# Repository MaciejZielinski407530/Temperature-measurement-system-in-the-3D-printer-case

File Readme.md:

Projekt: **System pomiaru temperatury w obudowie drukarki 3D**

W repozytorium znajduje się implementacja oraz projekt PCB stworzonego systemu. Udostępniona została również pełna doukemntacja projektu.
Do poprawnego działania wymagane są dodatkowe bilbioteki:
 -  SevenSeg: [Github](https://github.com/sigvaldm/SevenSeg)
 -  DS18B20: [Github](https://github.com/matmunk/DS18B20)
 -  OneWire: [Github](https://github.com/PaulStoffregen/OneWire)

Projekt oraz dokumentację projektową sporządził:

***Maciej Zieliński***

***Akademia Górniczo-Hutnicza Kraków***

-----------------------------------------------------------------------------------------------
Project: **Temperature measurement system in the 3D printer case**

The repository contains implementation and PCB project of the created system. Full documentation of the project was also made available.
Additional libraries are required for proper operation:
 -  SevenSeg: [Github](https://github.com/sigvaldm/SevenSeg)
 -  DS18B20: [Github](https://github.com/matmunk/DS18B20)
 -  OneWire: [Github](https://github.com/PaulStoffregen/OneWire)

The project and documentation prepared by:

***Maciej Zieliński***

***Akademia Górniczo-Hutnicza Kraków***

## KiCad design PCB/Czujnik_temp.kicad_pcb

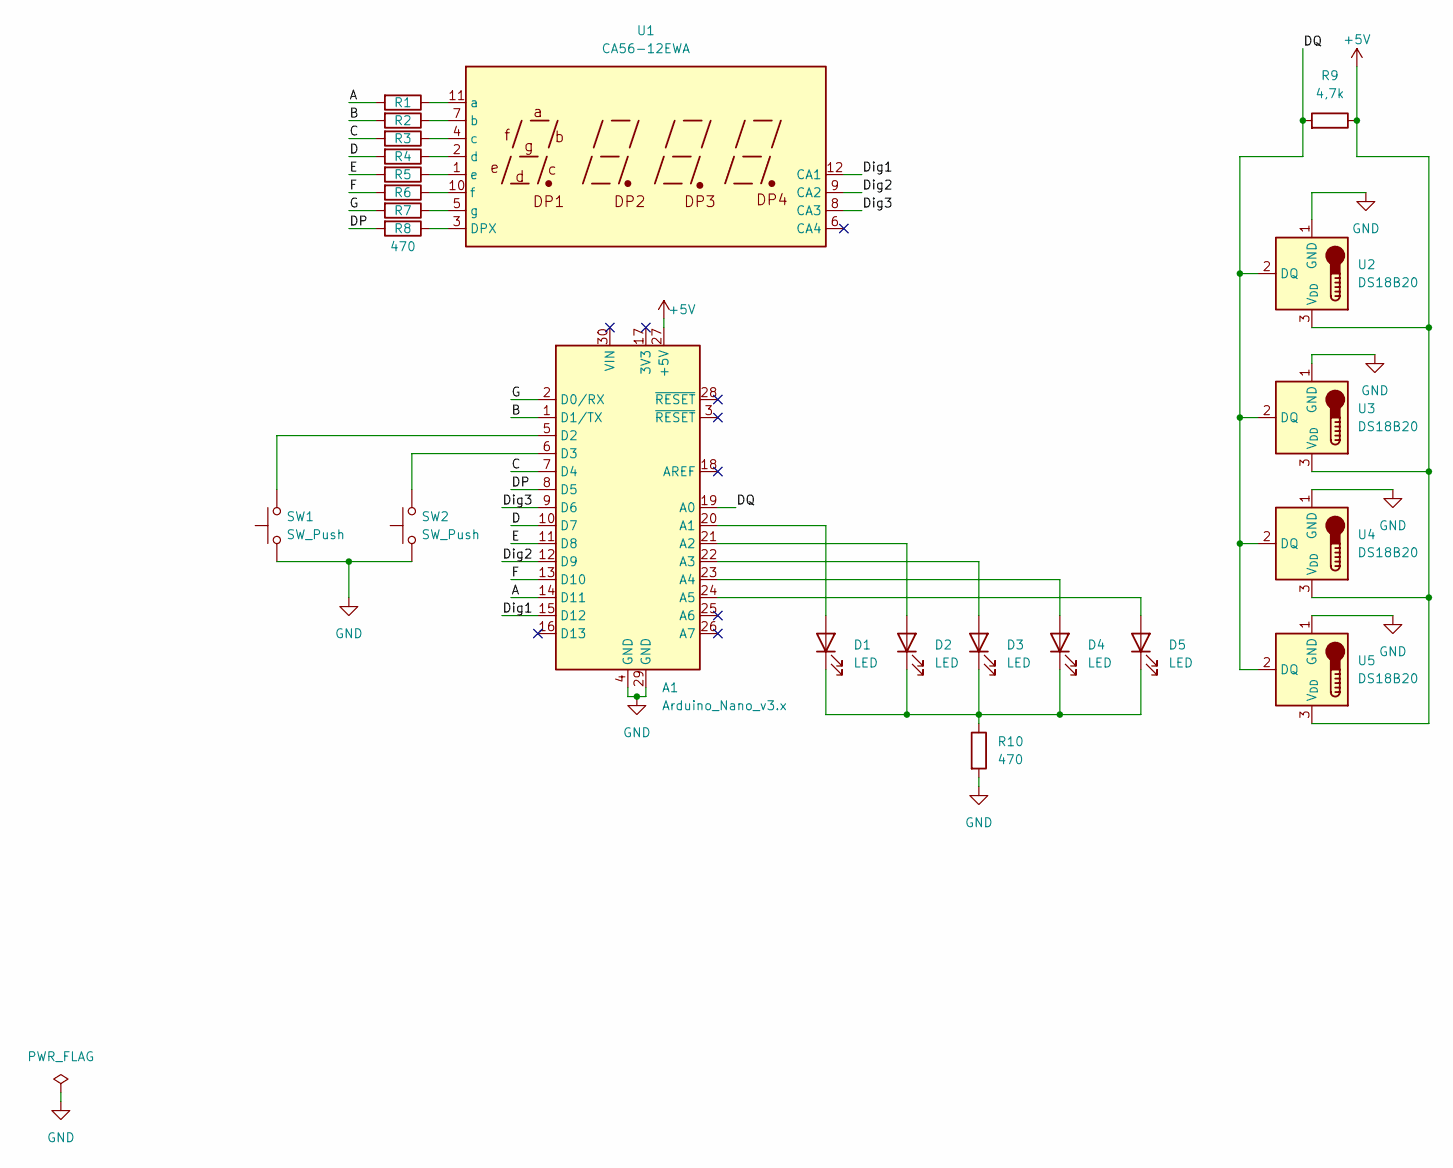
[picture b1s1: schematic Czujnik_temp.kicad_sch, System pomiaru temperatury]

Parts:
A1: Arduino_Nano_v3.x; Arduino_Nano
D1, D2, D3, D4, D5: LED; LED_D5.0mm
R1, R2, R3, R4, R5, R6, R8: R; R_Axial_DIN0207_L6.3mm_D2.5mm_P10.16mm_Horizontal
R7, R10: 470; R_Axial_DIN0207_L6.3mm_D2.5mm_P10.16mm_Horizontal
R9: 4,7k; R_Axial_DIN0207_L6.3mm_D2.5mm_P10.16mm_Horizontal
SW1, SW2: SW_Push; SW_PUSH_6mm_H9.5mm
U1: CA56-12EWA
U2, U3, U4, U5: DS18B20; TerminalBlock_bornier-3_P5.08mm

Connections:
+5V: A1.27 (+5V), R9.1, U2.3 (V_{DD}), U3.3 (V_{DD}), U4.3 (V_{DD}), U5.3 (V_{DD})
/A: A1.14 (D11), R1.2
/B: A1.1 (D1/TX), R2.2
/C: A1.7 (D4), R3.2
/D: A1.10 (D7), R4.2
/DP: A1.8 (D5), R8.2
/DQ: A1.19 (A0), R9.2, U2.2 (DQ), U3.2 (DQ), U4.2 (DQ), U5.2 (DQ)
/Dig1: A1.15 (D12), U1.12 (CA1)
/Dig2: A1.12 (D9), U1.9 (CA2)
/Dig3: A1.9 (D6), U1.8 (CA3)
/E: A1.11 (D8), R5.2
/F: A1.13 (D10), R6.2
/G: A1.2 (D0/RX), R7.2
GND: A1.4 (GND), A1.29 (GND), R10.2, SW1.1, SW2.1, U2.1 (GND), U3.1 (GND), U4.1 (GND), U5.1 (GND)
unnamed: A1.20 (A1), D1.2 (A)
unnamed: A1.21 (A2), D2.2 (A)
unnamed: A1.22 (A3), D3.2 (A)
unnamed: A1.23 (A4), D4.2 (A)
unnamed: A1.24 (A5), D5.2 (A)
unnamed: A1.5 (D2), SW1.2
unnamed: A1.6 (D3), SW2.2
unnamed: D1.1 (K), D2.1 (K), D3.1 (K), D4.1 (K), D5.1 (K), R10.1
unnamed: R8.1, U1.3 (DPX)
unnamed: R1.1, U1.11 (a)
unnamed: R2.1, U1.7 (b)
unnamed: R3.1, U1.4 (c)
unnamed: R4.1, U1.2 (d)
unnamed: R5.1, U1.1 (e)
unnamed: R6.1, U1.10 (f)
unnamed: R7.1, U1.5 (g)

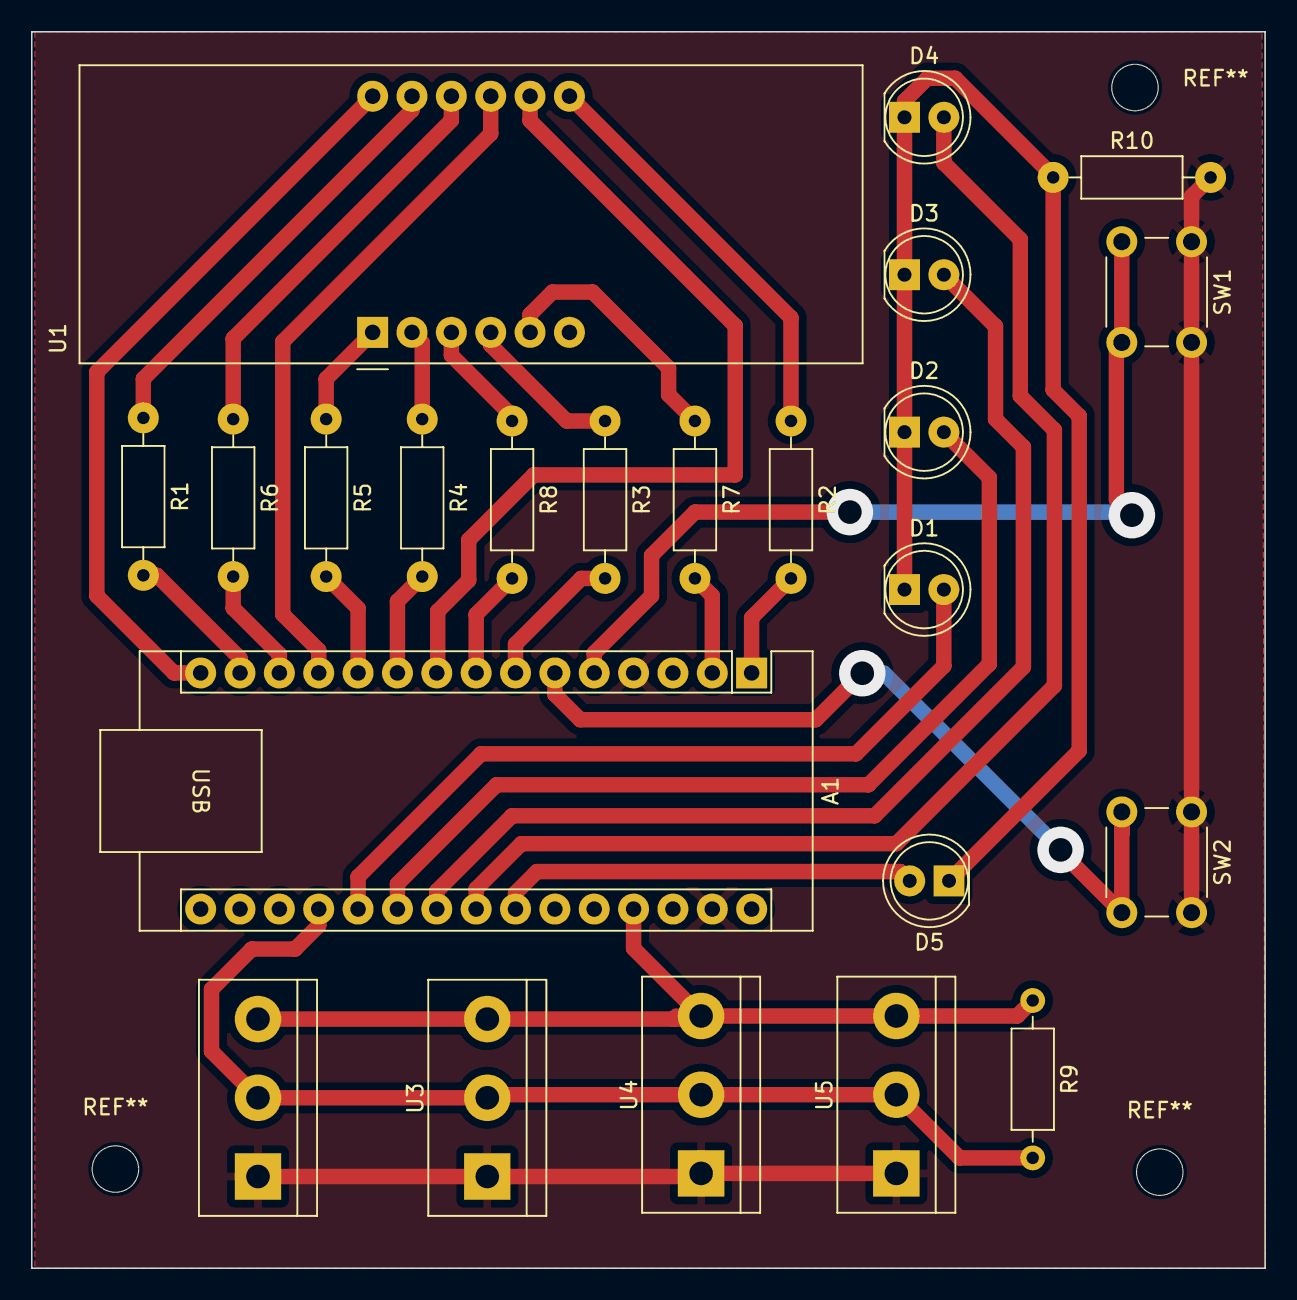
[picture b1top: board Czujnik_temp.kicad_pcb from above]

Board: 2 copper layers, 79.6 x 79.8 mm, 23 parts (0 on the bottom side), 30 nets.

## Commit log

2024-05-26 add project files
2024-05-29 Add PCB and implementation
2024-05-31 add documentation
